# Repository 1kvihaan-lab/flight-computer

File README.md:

# Stardance — ESP32-S3 Multi-Sensor Telemetry Board

A compact, single-board data logger built around an **ESP32-S3** class module with
**GNSS positioning**, **three-axis motion sensing**, **barometric altitude**, a
**battery-backed real-time clock**, and a **high-side current/power monitor**.

The board is designed to be built cheaply and in small volumes: two copper layers,
1.6 mm FR4, no impedance-controlled traces, no castellations, no fine-pitch
microvias. Everything on it can be assembled by a standard turnkey PCBA service
such as PCBWay.

---

## Table of contents

1. [What the board does](#what-the-board-does)
2. [At a glance](#at-a-glance)
3. [Functional blocks](#functional-blocks)
4. [Board mechanicals](#board-mechanicals)
5. [Power architecture](#power-architecture)
6. [Net and interface summary](#net-and-interface-summary)
7. [Bill of materials](#bill-of-materials)
8. [Fabrication notes](#fabrication-notes)
9. [Assembly notes](#assembly-notes)
10. [Cost estimate](#cost-estimate)
11. [Bring-up and test procedure](#bring-up-and-test-procedure)
12. [Firmware interface](#firmware-interface)
13. [Known issues](#known-issues)
14. [Design rules and constraints](#design-rules-and-constraints)
15. [Revision history](#revision-history)
16. [File inventory](#file-inventory)
17. [Licence](#licence)

---

## What the board does

Stardance is a **sensor fusion and position logger**. In one small board it
combines:

- an **ESP32-S3** module with onboard antenna — the compute, Wi-Fi and BLE radio,
- a **u-blox MAX-M10S** GNSS receiver — position, velocity and precise time,
- an **ADXL372** — high-g, low-power accelerometer for shock and impact events,
- an **LSM6DSOX** — 6-axis IMU for orientation and motion context,
- a **BMP388** — barometric pressure and temperature, for altitude,
- a **PCF8563T** RTC with a 32.768 kHz crystal — timekeeping across power cycles,
- an **INA228** — 20-bit current, voltage and power monitoring,
- a **USB-C** receptacle for power and data,
- an **AP2112K-3.3** LDO for the 3.3 V rail.

The design intent is a board that can answer, simultaneously: *where am I, how
fast am I moving, how did I get knocked around, how high am I, what time is it,
and how much energy have I actually used?* That combination is useful for
wearables, sports instrumentation, drone and rocket flight recorders, field
survey equipment, and any battery-powered device where you want to log motion
plus position plus power draw over a long deployment.

Because all of the sensors sit on shared I²C and SPI buses behind a single
microcontroller, the board can be configured at runtime for either a
high-rate short-duration capture (IMU at 1.6 kHz, streaming over USB/Wi-Fi) or a
low-rate long-duration log (one GNSS fix every few minutes, everything else in
its lowest-power mode, data to flash or SD).

---

## At a glance

| Parameter | Value |
| --- | --- |
| Board outline | **54.5 mm × 86.225 mm** (47.0 cm²) |
| Copper layers | **2** (F.Cu, B.Cu) |
| Board thickness | 1.6 mm |
| Surface finish | ENIG recommended (LGA land patterns) |
| Solder mask | Both sides, 0.05 mm mask expansion |
| Silkscreen | Both sides |
| Minimum via drill | 0.20 mm |
| Minimum track width used | 0.1124 mm |
| Largest / most critical part | ADXL372, 16-pad 3.0 × 3.25 mm LGA |
| Mounting | 4 × mounting holes |
| Programming | USB-C + 2 × 5 pin header |
| Design tool | KiCad |
| Source schematic | `StardancePCB.kicad_sch` |
| PCB file | `StardancB.kicad_pcb` |

---

## Functional blocks

### Compute and radio — ESP32-S3 module with onboard antenna

An ESP32-S3-based module carrying the SoC, flash, the RF front end and a PCB
antenna. Using the module rather than a bare chip keeps the RF layout off this
board entirely, which is what makes a two-layer design viable.

The module provides the SPI and I²C buses that all sensors hang from, the USB
peripheral used for programming and data streaming, and general-purpose I/O for
interrupts and control lines.

**Layout note:** the antenna end of the module overhangs or sits at the board
edge with a copper keep-out region beneath and beside it. Do not place metal,
battery or enclosure hardware in that zone, and do not pour ground under the
antenna. When the board is installed, the antenna side should face away from the
battery.

### GNSS — u-blox MAX-M10S

A concurrent multi-constellation GNSS receiver (GPS, GLONASS, Galileo, BeiDou)
with a very low tracking current. It talks over UART or I²C depending on
configuration, and needs a clean, well-decoupled supply — hence the dedicated
`/GNSS_VCC` rail rather than sharing the noisy 3.3 V sensor rail directly.

**Design notes:**

- Keep the GNSS supply trace short and well bypassed; GNSS receivers are
  sensitive to supply noise and to nearby switching regulators.
- The receiver needs a clear view of the sky. In an enclosure, the antenna must
  not be under metal.
- If no active antenna is fitted, provide an antenna connection (u.FL/SMA) per
  the module's reference design.
- The first fix after a cold start takes tens of seconds outdoors; this is
  normal and not a fault.

### Motion — ADXL372 and LSM6DSOX

Two complementary accelerometer devices:

- **ADXL372 (U11)** — a 3-axis, high-g accelerometer intended for impact and
  shock detection. It has an internal FIFO and an event engine, and it can wake
  the host on threshold. Its interrupt line `/ADXL_INT` and chip select
  `/ADXL_CS` are routed to the module; it shares SPI with the bus on `/SPI_SCK`.
- **LSM6DSOX** — a 6-axis accelerometer plus gyroscope with an embedded
  machine-learning core, used for orientation, gait or gesture classification
  and general motion context.

The split is deliberate: the ADXL372 is the shock witness and the LSM6DSOX is
the orientation reference, so an impact event does not saturate or corrupt the
data you use for attitude.

**Package note:** the ADXL372 in this design is the
`BCCZ` 16-terminal LGA, 3.0 × 3.25 mm (JEDEC CC-16-4). It is *not*
pin-compatible with the ADXL363, which shares the package outline, so do not
substitute one for the other in assembly. Pin 5 is `MISO` on one part and
reserved on the other, pin 7 and pin 8 also differ. The land pattern used here
is `PQFN50P322X300X114-16N`.

**Mask note:** the LGA apertures on this board are drawn 1:1 with the copper
pads, i.e. **zero solder-mask expansion**. This is intentional for LGA parts —
it prevents solder bridging between adjacent pads under the body — but it means
the fab must honour a zero mask expansion on those apertures rather than
applying its own default. Two DRC warnings about mask aperture bridging on these
pads are expected and accepted.

### Pressure and altitude — BMP388

A piezo-resistive absolute pressure sensor with temperature output. Used for
barometric altitude and for vertical-velocity estimation. It is sensitive to
light and to airflow, so the datasheet calls for a small vent or a light-blocking
underfill around the port. Relative altitude from barometric pressure drifts with
weather, so treat it as short-term relative altitude, not absolute height.

### Timekeeping — PCF8563T + 32.768 kHz crystal

An I²C real-time clock with a battery-backed supply so that time survives main
power removal. The crystal is an `FC-135`-style 32.768 kHz tuning-fork part in a
3.2 × 1.5 mm SMD package.

**Layout note:** the crystal is placed close to the RTC with short traces and a
local ground guard. Do not route high-speed signals under or beside it; a
tuning-fork crystal is a high-impedance resonator and will pick up coupling.

Time discipline: the ESP32-S3's own RTC is adequate for seconds-level accuracy
but drifts with temperature. The PCF8563 plus GNSS time on fix gives you a
board that always knows the correct time within a second or so of the last fix.

### Power monitoring — INA228

A 20-bit I²C current, bus-voltage and power monitor with an integrated charge and
energy accumulator. On this board it measures through a **10 mΩ shunt** on the
battery path, so it sees the real load current of the whole board rather than a
regulated rail current. The energy accumulator makes it possible to report
"joules consumed since boot" directly, which is a much more honest power figure
than multiplying an instantaneous reading by elapsed time.

Because the shunt is only 10 mΩ, the full-scale current range is set by the
INA228's programmable gain and the shunt value — check the configured range
against your expected peak current before trusting readings, since a large
inrush (the ESP32 waking and transmitting) can exceed a conservative setting.

### Power supply — AP2112K-3.3

A 600 mA low-dropout regulator providing the 3.3 V rail. It is a linear
regulator: simple, quiet, and low part count, at the cost of dissipating
`(Vin − 3.3) × Iload` as heat. With a Li-ion cell at 4.2 V and 200 mA of load
that is about 0.18 W, which is fine in free air but worth checking in a sealed
enclosure.

The regulator is deliberately used instead of a buck converter for the sensor
rail because GNSS and precision analogue measurements care more about supply
noise than about a few tens of milliwatts.

### USB-C and connectors

- **USB-C receptacle** — `HRO TYPE-C-31-M-12`, 14-pin USB 2.0-only variant. It
  provides 5 V in, USB 2.0 data to the module, and the usual CC pull-down
  resistors (5.1 kΩ) so that a USB-C host supplies 5 V. It is *not* a USB-PD
  port.
- **2 × 5 pin header** (`Conn_02x05_Odd_Even`) — debug / programming / expansion.
- **1 × 4 pin header** (`Conn_01x04_Pin`) — secondary connector, typically used
  for a serial console or an external sensor.
- **Test points** — several, for probing the main rails and buses during bring-up.
- **4 × mounting holes.**

---

## Board mechanicals

The board outline is a single rectangle on `Edge.Cuts`:

```
gr_rect (start 97.5 95.5) (end 152 181.725)
```

giving **54.5 mm × 86.225 mm**, or 46.99 cm².

- **Enclosure allowance:** if you are quoting or modelling an enclosure, allow
  about 55 × 87 mm internal, plus 0.5 mm clearance per side for the mask and
  routing tolerance, plus room for the USB-C overhang if the connector is
  flush-mounted.
- **Standoffs:** four mounting holes; use M2 or M2.5 hardware and keep the
  corresponding keep-out area free of components on the underside.
- **Antenna zone:** keep metal and battery out of the module antenna keep-out.
- **Connector access:** USB-C is at approximately (125, 175.5) in board
  coordinates — check that your enclosure gives it a suitable cutout and that
  the cable can plug in without strain.

---

## Power architecture

```
USB-C 5 V ──► /USB_5V ──┬──► AP2112K-3.3 ──► +3V3 ──► ESP32-S3, sensors, RTC
                        │
                        └──► charge path ──► /BAT_PROT ──► /BAT_LOAD ──► 10 mΩ shunt ──► INA228
```

- **`/USB_5V`** — raw 5 V from USB, present only when a cable is connected.
- **`/BAT_PROT`** — battery node downstream of protection (over-discharge and
  over-current), so the cell cannot be damaged by a firmware bug.
- **`/BAT_LOAD`** — the switched/monitored load side.
- **`+3V3`** — the regulated rail feeding the module and all sensors.
- **`/GNSS_VCC`** — a separately decoupled branch for the GNSS receiver so that
  the module's transmit bursts do not disturb the receiver's supply.
- A **Schottky diode** provides reverse-polarity and back-feed protection between
  the supply sources, and a **600 Ω @ 100 MHz ferrite bead** filters high-frequency
  noise out of a supply branch.

Practically: the board runs from USB alone, from a battery alone, or from both
with the battery charging. When you measure power with the INA228, remember that
USB presence changes the current path — log the USB state alongside the current
reading or the numbers will not make sense.

---

## Net and interface summary

| Net | Purpose |
| --- | --- |
| `+3V3` | Regulated 3.3 V rail |
| `/USB_5V` | 5 V from USB-C |
| `/BAT_PROT` | Protected battery node |
| `/BAT_LOAD` | Monitored battery load node |
| `/GNSS_VCC` | Filtered supply for the GNSS receiver |
| `I2C_SDA` / `I2C_SCL` | Shared I²C bus (BMP388, LSM6DSOX, PCF8563T, INA228) |
| `SPI_SCK` | Shared SPI clock (ADXL372) |
| `/ADXL_CS` | ADXL372 chip select |
| `/ADXL_INT` | ADXL372 interrupt / event line |
| `/PWM2` | General-purpose PWM output |

The I²C bus carries several devices with different addresses; confirm the address
straps (the `SA0`/`SDO` style pins) do not collide before writing firmware.

---

## Bill of materials

The table below lists the significant parts. Quantities for passives are
approximate because the exact count comes from the KiCad position file; the
authoritative BOM is the one exported from the schematic.

| Ref | Part | Function | Qty | Est. unit price (10-off) |
| --- | --- | --- | --- | --- |
| U? | ESP32-S3 module, onboard antenna, SMD | MCU + Wi-Fi/BLE | 1 | $4 – $6 |
| U? | MAX-M10S | GNSS receiver | 1 | $14 – $20 |
| U11 | ADXL372BCCZ-RL7 | High-g accelerometer | 1 | $14 – $20 |
| U? | LSM6DSOX | 6-axis IMU | 1 | $4 – $7 |
| U? | BMP388 | Pressure / altitude | 1 | $2.50 – $4 |
| U? | PCF8563T | RTC | 1 | $1 – $2 |
| Y1 | FC-135 32.768 kHz, 3.2 × 1.5 mm | RTC crystal | 1 | $0.50 – $1 |
| U? | INA228 | Current / power monitor | 1 | $5 – $8 |
| U? | AP2112K-3.3 | 3.3 V LDO | 1 | $0.25 – $0.50 |
| J? | USB-C receptacle, HRO TYPE-C-31-M-12 | Power + data | 1 | $0.80 – $1.50 |
| J? | `Conn_02x05_Odd_Even` | Debug / expansion | 1 | $0.30 – $0.80 |
| J? | `Conn_01x04_Pin` | Auxiliary | 1 | $0.20 – $0.50 |
| R? | 10 mΩ shunt | Current sense | 1 | $0.30 – $1.00 |
| D? | Schottky diode | Reverse / back-feed protection | 1 | $0.20 – $0.60 |
| FB? | 600 Ω @ 100 MHz ferrite | Supply filtering | 1 | $0.05 – $0.20 |
| — | Passives: 10 k, 100 k, 100 R, 52.3 k, 5.1 k, 4.7 k, 1 µF, 100 nF, 10 nF, 15 pF, 4.7 nF, 10 µF, 22 µF | Decoupling, pull-ups, filters, timing | ~55 – 70 | $1.50 – $3.00 total |
| — | Test points, mounting holes | Bring-up / mechanical | ~9 | negligible |

**Estimated parts cost: $50 – $75 per board** at 10-off distributor pricing.
Most of that cost sits in three parts: the GNSS receiver, the ADXL372, and the
ESP32-S3 module. Everything else is small change.

Notes:

- `52.3 k` and `15 pF` are typical GNSS/oscillator or divider values — check them
  against the reference design of the specific module variant you buy.
- `5.1 k` on the USB-C CC pins is mandatory; without it a USB-C host will not
  supply 5 V.
- The 10 mΩ shunt should be a low-TCR, low-inductance part; a generic thick-film
  resistor will give you temperature- and frequency-dependent current readings.

---

## Fabrication notes

Send these with the order, or attach them as a README in the fab package:

1. **Layers:** 2, 1.6 mm thick, 1 oz copper both sides.
2. **Finish:** ENIG. The two LGA land patterns and the fine-pitch parts benefit
   from a flat finish; HASL is acceptable but makes LGA placement less reliable.
3. **Mask:** standard, **but honour the 1:1 (zero-expansion) apertures on the
   ADXL372 and LGA pads**. Do not apply a global mask expansion on those.
4. **Min drill:** 0.20 mm — this meets the standard 0.20 mm minimum CNC drill at
   the usual low-cost services. Do not request 0.15 mm drills.
5. **Impedance control:** not required.
6. **Castellations:** none.
7. **Panelisation:** the board is 54.5 mm on the short edge. Ask the fab whether
   it will be panelised; if so, confirm the mouse-bite or V-score positions and
   that no components sit within the breakaway zone.
8. **Silkscreen:** keep clear of pads; the reference designators are needed for
   hand rework.
9. **Edge clearance:** confirm no copper closer than 0.3 mm to the outline.

Deliver: Gerbers (RS-274X), Excellon drill file, and a fab drawing. Include the
board thickness and finish in the fab drawing rather than relying on file names.

---

## Assembly notes

The assembly is a straightforward single-sided SMT job plus a USB-C connector.

- **Sides:** all SMT parts on the top side. No bottom-side SMT, so no double
  reflow and no second stencil.
- **Joints:** roughly 220 – 260 SMT joints, dominated by passives.
- **Unique parts:** roughly 70 – 85 line items including passives.
- **Process:** lead-free reflow, IPC-A-610 Class 2 is sufficient for a prototype.
- **THT:** the headers and any through-hole parts can be hand-soldered or
  wave-soldered; specify which.
- **Turnkey vs consigned:** turnkey (the assembler sources the parts) is simpler
  and avoids shipping reels around, but you pay a markup and you inherit their
  stock risk. Consigned (you buy from a distributor and ship the parts) is
  cheaper on parts but shifts the logistics and any shortage onto you.

**Parts to check for stock before you commit:** the MAX-M10S and the ADXL372 are
the two expensive, long-lead items on this board. Ask for a stock date before
confirming a build date, and if either is out of stock, decide up front whether
you will accept a substitute — for the ADXL372, there is no drop-in equivalent
in the same footprint.

---

## Cost estimate

Prices below are ballpark figures for a small prototype run through a turnkey
PCBA service (PCBWay or equivalent). They are for budgeting only; the real
number comes from the vendor's generated quote.

### Two boards

| Line | Basis | Estimate |
| --- | --- | --- |
| PCB fabrication | Minimum order is typically 5 pcs; 10 pcs of this size is ~$5 | $5 – $10 |
| Assembly setup + stencil + labour | One-time setup dominates at this quantity | $80 – $120 |
| Components | 2 – 5 sets, see BOM | $100 – $150 |
| Shipping (DHL/FedEx) | ~1 kg | $40 – $60 |
| **Total** | | **$230 – $350** |
| Realistic outcome | Assemblers have a 5-piece minimum | **~$300 for 5 boards** |

### Ten boards

| Line | Estimate |
| --- | --- |
| PCB fabrication | $5 – $30 |
| Assembly (setup + labour) | $150 – $250 |
| Components (10 sets) | $500 – $750 |
| Shipping | $40 – $80 |
| **Total** | **$700 – $1,100** |
| **Unit cost** | **$70 – $110 per board** |

The important lesson from both tables: **at prototype quantities the PCB is
almost free and the money is in parts and assembly setup.** Unit cost falls
mainly by spreading the setup fee — at 50 pcs the setup cost per board drops by
roughly 5×, and component pricing improves another 15 – 30 %.

To get a vendor quote, fill in the PCBA form with approximately **250 SMT
joints** and **75 unique parts**, 2 layers, 54.5 × 86.23 mm, and turnkey
sourcing. Save the resulting PDF quote with its date so the number is traceable.

---

## Bring-up and test procedure

Do these in order. Do not skip steps — a fault found at step 9 costs you a whole
board, and a fault found at step 3 costs you a resistor.

### 1. Visual inspection, unpowered

- Check for solder bridges on the two LGA parts, the USB-C pins, and the fine
  passives. Use a microscope; the LGA pitch is too fine for naked-eye inspection.
- Confirm no components are missing or rotated, and that polarity marks match.
- Confirm no copper slivers or unplated edges.

### 2. Continuity, unpowered

- `+3V3` to `GND`: should read high resistance (tens of kΩ or more), not a short.
- `/USB_5V` to `GND`: same.
- `/BAT_PROT` to `/BAT_LOAD`: should read approximately the shunt value plus the
  protection path resistance.
- Every I²C and SPI line to `GND`: no shorts.

If `+3V3` reads a short, find it before applying power.

### 3. First power, current-limited

- Apply 5 V from a bench supply **with the current limit set to about 100 mA**.
- Watch the draw. A healthy idle board draws a few tens of mA; a board that
  slams into the limit has a short.
- Measure `+3V3` — should be 3.28 – 3.32 V.
- Measure `/GNSS_VCC` — should be present and close to 3.3 V.

### 4. USB enumeration

- Connect to a PC over USB-C. The ESP32-S3 should enumerate (native USB or a
  USB-serial bridge, depending on the module variant).
- Confirm 5 V is present on `/USB_5V` and the CC pull-downs are working — a
  USB-C-to-C cable from a USB-C host is the strict test; an A-to-C cable will
  work even with the CC resistors missing.

### 5. Module boot and programming

- Program a blink or serial-print sketch over USB.
- Confirm the module boots and the serial console works at the expected baud.
- Confirm the 2 × 5 header gives you access to the boot/reset lines if you use
  them.

### 6. I²C bus scan

- Scan the I²C bus and confirm every device answers at its expected address:
  BMP388, LSM6DSOX, PCF8563T, INA228.
- A missing device means a solder joint, a wrong address strap, or a
  non-populated part. A device answering at an unexpected address means an
  address pin is strapped differently than assumed.

### 7. Sensor sanity

- Read die temperature from each device — they should agree within a few degrees
  and match room temperature.
- Read the BMP388 pressure — near 1013 hPa at sea level, and it should change
  when you gently press or release near the port.
- Read the LSM6DSOX accelerometer — with the board flat, one axis reads about
  1 g; tilt the board and watch the vector rotate.
- Read the ADXL372 — confirm it responds on SPI and that `/ADXL_INT` toggles
  when you tap the board.
- Read the RTC — set a time, remove power for a minute, restore power, and
  confirm the time kept running.

### 8. Power monitor calibration

- With a known resistive load, compare the INA228 current reading against a
  multimeter in series.
- Confirm the sign convention, the shunt value in the configuration register,
  and the full-scale range. A wrong shunt value in firmware gives readings that
  are off by a constant factor — check it now, not later.

### 9. GNSS

- Go outdoors with a clear sky view. Cold start to first fix typically takes
  20 – 60 seconds. If you get no fix in five minutes outdoors, check the supply,
  the antenna connection and the UART/I²C configuration.
- Confirm the reported time matches reality to within a second.
- Compare the reported position to a known point.

### 10. Radio

- Confirm Wi-Fi association and BLE advertising.
- Check RSSI at a few metres. A weak or absent signal usually means metal or a
  battery over the antenna keep-out.

### 11. Thermal

- Run the board for ten minutes at your expected load and check the LDO and the
  module temperature by touch or IR. The LDO is the part that will get warm.

Record every measurement. A bring-up log with nominal values makes the second
board far easier to debug.

---

## Firmware interface

Firmware is not included in this repository; this section documents what the
hardware expects.

| Peripheral | Bus | Pins / nets | Notes |
| --- | --- | --- | --- |
| ESP32-S3 module | — | — | Native USB or bridge UART for programming |
| MAX-M10S | UART or I²C | `/GNSS_VCC` supply | Configure protocol at init |
| ADXL372 | SPI | `SPI_SCK`, `/ADXL_CS`, `/ADXL_INT` | Interrupt is the cheap way to detect impacts |
| LSM6DSOX | I²C | `I2C_SDA`, `I2C_SCL` | Optional interrupt pin if wired |
| BMP388 | I²C | `I2C_SDA`, `I2C_SCL` | Needs a conversion-time delay between reads |
| PCF8563T | I²C | `I2C_SDA`, `I2C_SCL` | Battery-backed; set once, read thereafter |
| INA228 | I²C | `I2C_SDA`, `I2C_SCL` | Configure shunt value and range before reading |
| PWM output | GPIO | `/PWM2` | General purpose |

Practical firmware advice:

- **Initialise I²C once, share the bus.** All four I²C devices live on the same
  two wires. Take a mutex or serialise access, or a long sensor read will
  collide with an RTC read and one of them will return garbage.
- **Use the ADXL372 FIFO**, not a polling loop. Polling a high-g part at high
  rate wakes the CPU constantly and burns the battery you are trying to measure.
- **Use GNSS time to discipline the RTC.** The RTC is accurate to tens of ppm;
  GNSS gives you absolute time. Re-sync on every fix.
- **Log the USB state with the current reading.** Otherwise your power data has
  an unexplained step in it wherever a cable was plugged in.
- **Deep sleep order matters.** Put the sensors to sleep first, then the GNSS,
  then the module. A sensor left in continuous-conversion mode will hold the
  rail up and defeat the point of sleeping.

---

## Known issues

These are open items on Rev B. Fix them before ordering a production batch.

1. **DRC is not clean.** The last full design-rule check reported unconnected
   pads in the double digits and several copper clearance violations. Unconnected
   pads mean the netlist and the layout disagree; on a two-layer board these are
   usually a forgotten via or a trace that stops one grid unit short. Run
   *Inspect → Clearance* and *Routing → Track Cleanup* and re-run DRC until it
   is empty.
2. **Solder-mask aperture bridge warnings on the LGA pads.** Expected and
   accepted: the apertures are intentionally 1:1 with the copper to prevent
   bridging under the body. Note this explicitly in the fab notes so the fab
   does not "fix" it.
3. **ERC power-output conflicts.** Multiple power-output pins on the same net
   (the regulator output pins and the GND pins on one device) plus a `PWR_FLAG`
   produce "power output and power output" errors. These are benign in KiCad
   when the pins genuinely are paralleled outputs; confirm each one rather than
   suppressing the class globally.
4. **ADXL372 land pattern provenance.** The footprint came from a
   vendor-supplied library (`PQFN50P322X300X114-16N`). Verify the pad
   dimensions and the pin-1 orientation against the ADXL372 datasheet land
   pattern before assembly — a mirrored LGA is not always visually obvious.
5. **No reverse-polarity protection on the battery connector** beyond the
   Schottky in the supply path. Confirm the connector keying physically prevents
   reverse insertion, or add a P-FET.
6. **Thermal margin of the LDO is unverified** in a sealed enclosure at full
   load. Measure before committing to a battery-only, enclosed deployment.
7. **USB-C is USB 2.0 only.** No USB-PD negotiation and no SuperSpeed. Do not
   design a charging scheme that assumes higher voltage.

---

## Design rules and constraints

The board was designed to clear the cheapest fabrication tier at common
low-cost fabs.

| Rule | Value used | Constraint |
| --- | --- | --- |
| Layers | 2 | 2-layer tier |
| Board size | 54.5 × 86.225 mm | under the 100 × 100 mm price tier |
| Min track | 0.1124 mm | above 0.10 mm |
| Min via drill | 0.20 mm | at the 0.20 mm standard minimum |
| Min via annular ring | standard | — |
| Mask expansion | 0.05 mm global, 0 mm on LGA | — |
| Board thickness | 1.6 mm | standard |
| Copper weight | 1 oz | standard |

Two-layer design consequences worth remembering: there is no solid ground plane
under the whole board, so return currents must follow their traces. Keep the
GNSS supply and the crystal traces short, keep the SPI clock away from the
crystal and the GNSS supply, and do not route signals across a plane split.

---

## Revision history

| Rev | Date | Change | Status |
| --- | --- | --- | --- |
| A | — | Initial layout | Superseded |
| B | 2026-10-29 | Two-layer rework, sensor set consolidated, LGA mask apertures set to 1:1 | DRC open, not yet built |

---

## File inventory

| File | Description |
| --- | --- |
| `StardancePCB.kicad_sch` | KiCad schematic (source of truth for the netlist) |
| `StardancB.kicad_pcb` | KiCad PCB layout, Rev B |
| `README.md` | This document |

When you generate the fabrication package, include the Gerbers, the Excellon
drill file, the BOM export, and the position (pick-and-place) file.

---

## Licence

Add your preferred licence here. For open hardware, CERN-OHL-P or CERN-OHL-S is
the usual choice; for a permissive hardware-plus-documentation release,
Apache-2.0 for the design files plus CC-BY-4.0 for the documentation also works.

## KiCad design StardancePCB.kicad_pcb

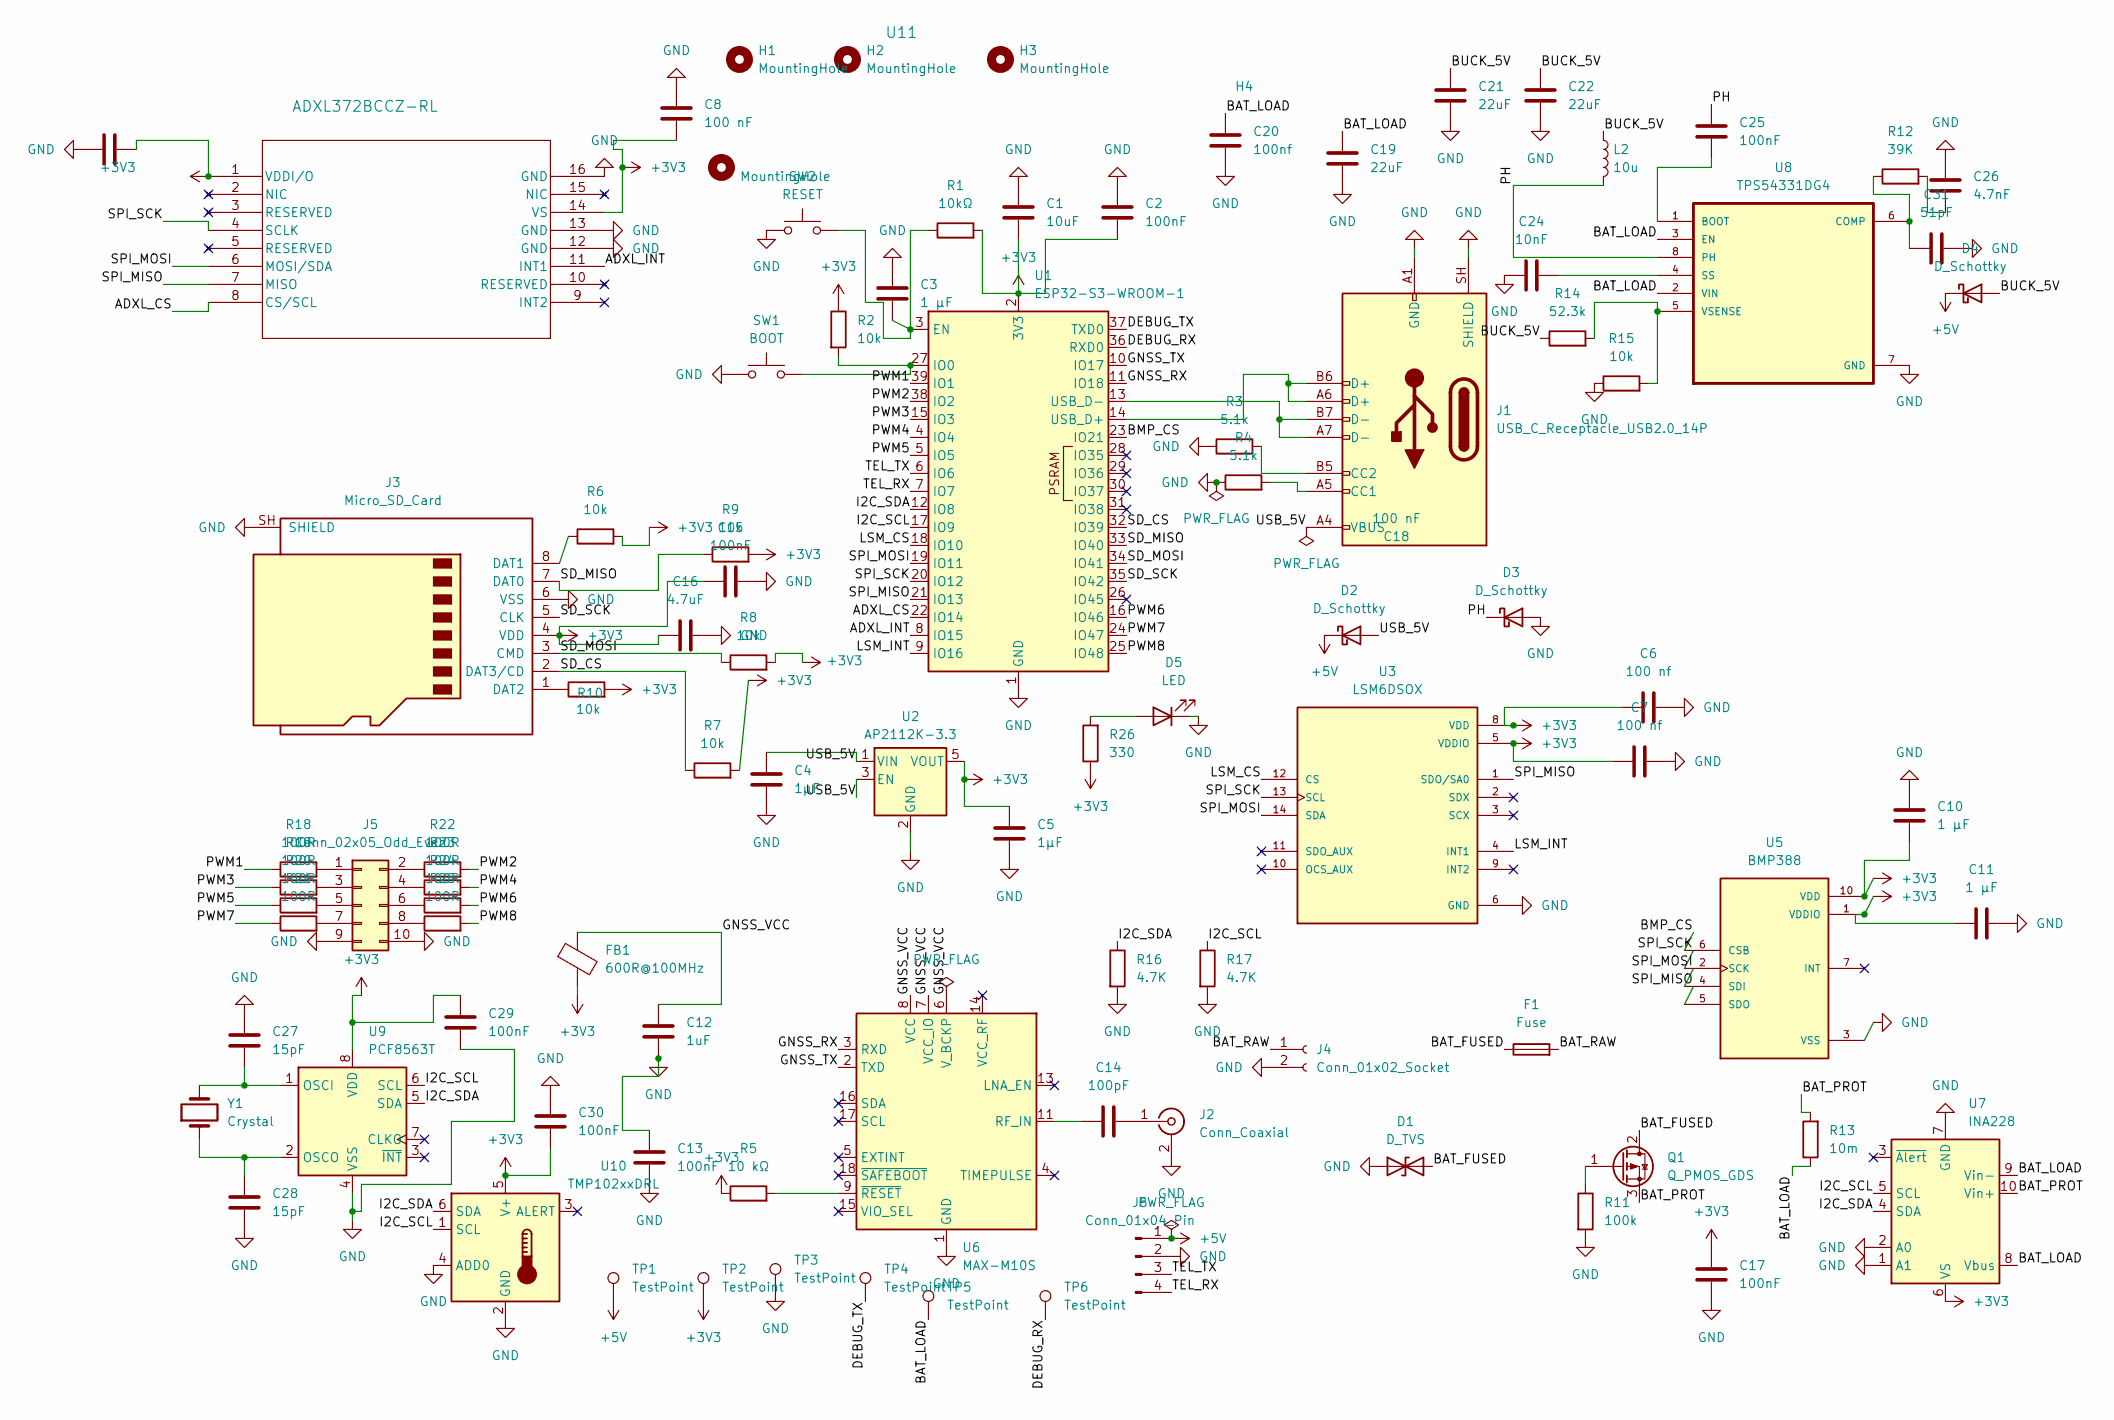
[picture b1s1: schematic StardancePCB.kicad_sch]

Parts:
C1: 10uF; C_0805_2012Metric
C2, C13, C15, C17, C25, C29, C30: 100nF; C_0603_1608Metric
C3, C10, C11: 1 µF; C_0603_1608Metric
C4, C5: 1µF; C_0603_1608Metric
C6, C7: 100 nf; C_0603_1608Metric
C8, C18: 100 nF; C_0603_1608Metric
C12: 1uF; C_0603_1608Metric
C14: 100pF; C_0603_1608Metric
C16: 4.7uF; C_0603_1608Metric
C19, C21, C22: 22uF; C_1206_3216Metric
C20: 100nf; C_0603_1608Metric
C24: 10nF; C_0603_1608Metric
C26: 4.7nF; C_0603_1608Metric
C27, C28: 15pF; C_0603_1608Metric
C31: 51pF; C_0603_1608Metric
D1: D_TVS; D_SMA
D2, D3, D4: D_Schottky; D_SMA
D5: LED; LED_0805_2012Metric
F1: Fuse; Fuse_1206_3216Metric
FB1: 600R@100MHz; L_0805_2012Metric
H1, H2, H3, H4: MountingHole; MountingHole_3.2mm_M3
J1: USB_C_Receptacle_USB2.0_14P; USB_C_Receptacle_HRO_TYPE-C-31-M-12
J2: Conn_Coaxial; U.FL_Hirose_U.FL-R-SMT-1_Vertical
J3: Micro_SD_Card; microSD_HC_Hirose_DM3AT-SF-PEJM5
J4: Conn_01x02_Socket; PinSocket_1x02_P2.54mm_Vertical
J5: Conn_02x05_Odd_Even; PinHeader_2x05_P2.54mm_Vertical
J6: Conn_01x04_Pin; PinHeader_1x04_P2.54mm_Vertical
L2: 10u; L_7.3x7.3_H3.5
Q1: Q_PMOS_GDS; SOT-23
R1: 10kΩ; R_0603_1608Metric
R2, R6, R7, R8, R9, R10, R15: 10k; R_0603_1608Metric
R3, R4: 5.1k; R_0603_1608Metric
R5: 10 kΩ; R_0603_1608Metric
R11: 100k; R_0603_1608Metric
R12: 39K; R_0603_1608Metric
R13: 10m; R_2512_6332Metric
R14: 52.3k; R_0603_1608Metric
R16, R17: 4.7K; R_0603_1608Metric
R18, R19, R20, R21, R22, R23, R24, R25: 100R; R_0603_1608Metric
R26: 330; R_0603_1608Metric
SW1: BOOT; SW_PUSH_6mm
SW2: RESET; SW_PUSH_6mm
TP1, TP2, TP3, TP4, TP5, TP6: TestPoint; TestPoint_Pad_1.5x1.5mm
U1: ESP32-S3-WROOM-1
U2: AP2112K-3.3; SOT-23-5
U3: LSM6DSOX; LGA-14_3x2.5mm_P0.5mm_LayoutBorder3x4y; PARTREV 3.0
U5: BMP388; XDCR_BMP388; PARTREV 1.7
U6: MAX-M10S; ublox_MAX
U7: INA228; TSSOP-10_3x3mm_P0.5mm
U8: TPS54331DG4; SOIC127P599X175-8N
U9: PCF8563T; SOIC-8_3.9x4.9mm_P1.27mm
U10: TMP102xxDRL; SOT-563
U11: ADXL372BCCZ-RL; PQFN50P322X300X114-16N
Y1: Crystal; Crystal_SMD_3215-2Pin_3.2x1.5mm

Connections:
+3V3: C1.2, C2.2, C5.1, C6.1, C7.1, C8.2, C10.2, C11.1, C15.1, C16.1, C17.1, C18.2, C29.1, C30.2, FB1.2, J3.4 (VDD), R1.2, R2.1, R5.1, R6.2, R7.2, R8.2, R9.2, R10.2, R26.1, TP2.1 (1_1), U1.2 (3V3), U2.5 (VOUT), U3.5 (VDDIO), U3.8 (VDD), U5.1 (VDDIO), U5.10 (VDD), U7.6 (VS), U9.8 (VDD), U10.5 (V+), U11.1 (VDDI/O), U11.14 (VS); also elsewhere on the board
+5V: D2.1 (K), D4.1 (K), J6.1, TP1.1 (1_1)
/ADXL_CS: U1.22 (IO14), U11.8 (CS/SCL)
/ADXL_INT: U1.8 (IO15), U11.11 (INT1)
/BAT_FUSED: D1.2 (A2), F1.1, Q1.2 (D)
/BAT_LOAD: C19.1, C20.1, R13.1, TP5.1 (1_1), U7.8 (Vbus), U7.9 (Vin-), U8.2 (VIN), U8.3 (EN)
/BAT_PROT: Q1.3 (S), R13.2, U7.10 (Vin+)
/BAT_RAW: F1.2, J4.1
/BMP_CS: U1.23 (IO21), U5.6 (CSB)
/BUCK_5V: C21.1, C22.1, D4.2 (A), L2.1, R14.1
/DEBUG_RX: TP6.1 (1_1), U1.36 (RXD0)
/DEBUG_TX: TP4.1 (1_1), U1.37 (TXD0)
/GNSS_RX: U1.11 (IO18), U6.3 (RXD)
/GNSS_TX: U1.10 (IO17), U6.2 (TXD)
/GNSS_VCC: C12.1, FB1.1, U6.6 (V_BCKP), U6.7 (VCC_IO), U6.8 (VCC)
/I2C_SCL: R17.1, U1.17 (IO9), U7.5 (SCL), U9.6 (SCL), U10.1 (SCL)
/I2C_SDA: R16.1, U1.12 (IO8), U7.4 (SDA), U9.5 (SDA), U10.6 (SDA)
/LSM_CS: U1.18 (IO10), U3.12 (CS)
/LSM_INT: U1.9 (IO16), U3.4 (INT1)
/PH: C25.1, D3.1 (K), L2.2, U8.8 (PH)
/PWM1: R18.1, U1.39 (IO1)
/PWM2: R22.2, U1.38 (IO2)
/PWM3: R19.1, U1.15 (IO3)
/PWM4: R23.2, U1.4 (IO4)
/PWM5: R20.1, U1.5 (IO5)
/PWM6: R24.2, U1.16 (IO46)
/PWM7: R21.1, U1.24 (IO47)
/PWM8: R25.2, U1.25 (IO48)
/SD_CS: J3.2 (DAT3/CD), R7.1, U1.32 (IO39)
/SD_MISO: J3.7 (DAT0), R9.1, U1.33 (IO40)
/SD_MOSI: J3.3 (CMD), R8.1, U1.34 (IO41)
/SD_SCK: J3.5 (CLK), U1.35 (IO42)
/SPI_MISO: U1.21 (IO13), U3.1 (SDO/SA0), U5.5 (SDO), U11.7 (MISO)
/SPI_MOSI: U1.19 (IO11), U3.14 (SDA), U5.4 (SDI), U11.6 (MOSI/SDA)
/SPI_SCK: U1.20 (IO12), U3.13 (SCL), U5.2 (SCK), U11.4 (SCLK)
/TEL_RX: J6.4, U1.7 (IO7)
/TEL_TX: J6.3, U1.6 (IO6)
/USB_5V: C4.1, D2.2 (A), J1.A4 (VBUS), J1.A9 (VBUS), J1.B4 (VBUS), J1.B9 (VBUS), U2.1 (VIN), U2.3 (EN)
GND: C1.1, C2.1, C3.1, C4.2, C5.2, C6.2, C7.2, C8.1, C10.1, C11.2, C12.2, C13.1, C13.2, C15.2, C16.2, C17.2, C18.1, C19.2, C20.2, C21.2, C22.2, C24.1, C26.1, C27.1, C28.2, C29.2, C30.1, C31.2, D1.1 (A1), D3.2 (A), D5.1 (K), J1.A1 (GND), J1.A12 (GND), J1.B1 (GND), J1.B12 (GND), J1.SH (SHIELD), J2.2 (Ext), J3.6 (VSS), J3.SH (SHIELD), J4.2, J5.9, J5.10, J6.2, R3.1, R4.1, R11.2, R15.1, R16.2, R17.2, SW1.1, SW2.1, TP3.1 (1_1), U1.1 (GND), U1.40 (GND), U1.41 (GND), U2.2 (GND), U3.6 (GND), U3.7 (GND), U5.3 (VSS), U5.8 (VSS), U5.9 (VSS), U6.1 (GND), U6.10 (GND), U6.12 (GND), U7.1 (A1), U7.2 (A0), U7.7 (GND), U8.7 (GND), U9.4 (VSS), U10.2 (GND), U10.4 (ADD0), U11.12 (GND), U11.13 (GND), U11.16 (GND); also elsewhere on the board
unnamed: C26.2, R12.2
unnamed: D5.2 (A), R26.2
unnamed: J1.A5 (CC1), R4.2
unnamed: J1.B5 (CC2), R3.2
unnamed: C14.2, J2.1 (In)
unnamed: J3.8 (DAT1), R6.1
unnamed: J3.1 (DAT2), R10.1
unnamed: J5.1, R18.2
unnamed: J5.2, R22.1
unnamed: J5.3, R19.2
unnamed: J5.4, R23.1
unnamed: J5.5, R20.2
unnamed: J5.6, R24.1
unnamed: J5.7, R21.2
unnamed: J5.8, R25.1
unnamed: Q1.1 (G), R11.1
unnamed: C3.2, R1.1, SW2.2, U1.3 (EN)
unnamed: R2.2, SW1.2, U1.27 (IO0)
unnamed: J1.A6 (D+), J1.B6 (D+), U1.14 (USB_D+)
unnamed: J1.A7 (D-), J1.B7 (D-), U1.13 (USB_D-)
unnamed: C14.1, U6.11 (RF_IN)
unnamed: R5.2, U6.9 (~RESET)
unnamed: C25.2, U8.1 (BOOT)
unnamed: C31.1, R12.1, U8.6 (COMP)
unnamed: C24.2, U8.4 (SS)
unnamed: R14.2, R15.2, U8.5 (VSENSE)
unnamed: C27.2, U9.1 (OSCI), Y1.2
unnamed: C28.1, U9.2 (OSCO), Y1.1

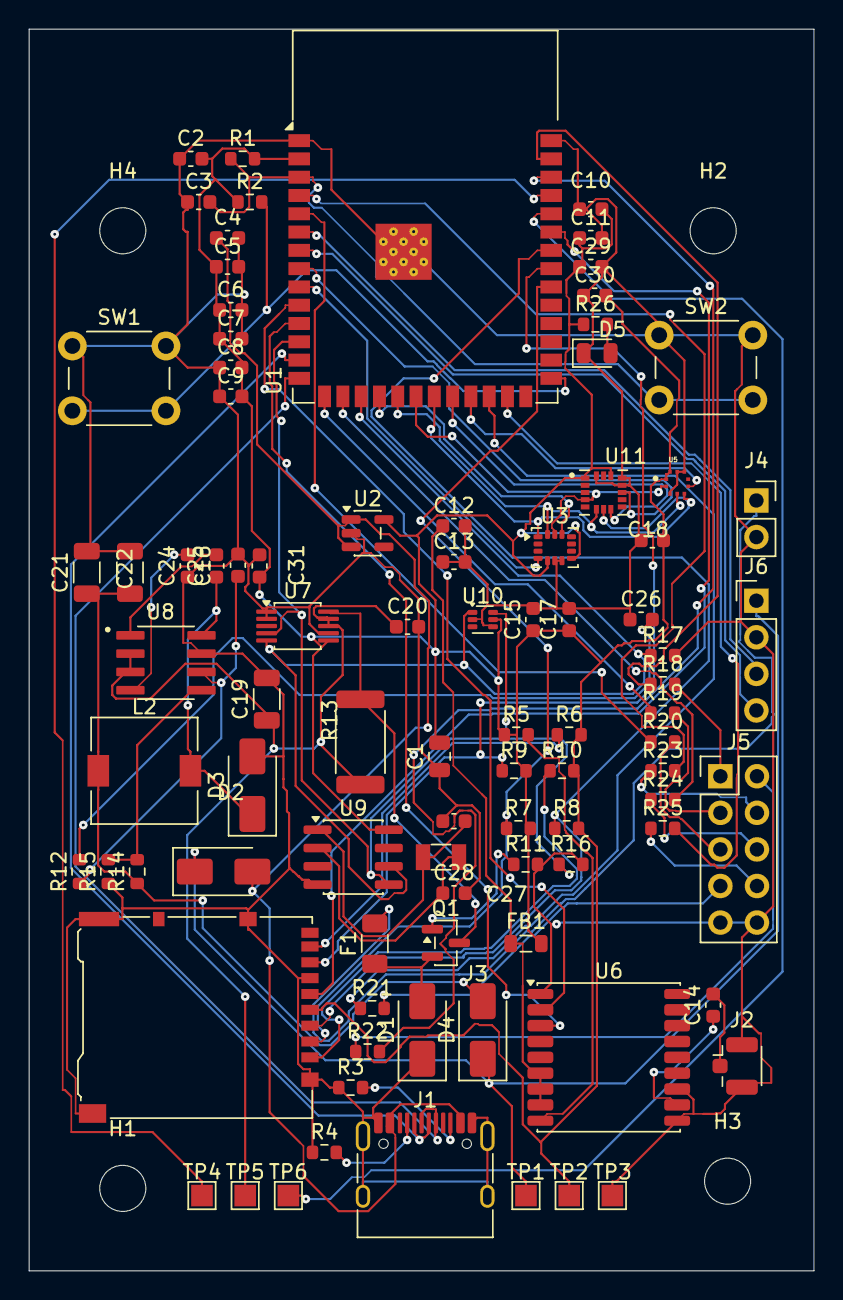
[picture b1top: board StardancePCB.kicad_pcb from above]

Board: 2 copper layers, 54.5 x 86.2 mm, 94 parts (0 on the bottom side), 67 nets.

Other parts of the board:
C9: 100 nF; C_0603_1608Metric

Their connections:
+3V3: C9.2; also elsewhere on the board
GND: C9.1; also elsewhere on the board

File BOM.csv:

"Id";"Designator";"Footprint";"Quantity";"Designation";"Supplier and ref";
1;"C1";"C_0805_2012Metric";1;"10uF";;;
2;"C2, C13, C15, C17, C25, C29, C30";"C_0603_1608Metric";7;"100nF";;;
3;"C3, C10, C11";"C_0603_1608Metric";3;"1 µF";;;
4;"C4, C5";"C_0603_1608Metric";2;"1µF";;;
5;"C6, C7";"C_0603_1608Metric";2;"100 nf";;;
6;"C8, C9, C18";"C_0603_1608Metric";3;"100 nF";;;
7;"C12";"C_0603_1608Metric";1;"1uF";;;
8;"C14";"C_0603_1608Metric";1;"100pF";;;
9;"C16";"C_0603_1608Metric";1;"4.7uF";;;
10;"C19, C21, C22";"C_1206_3216Metric";3;"22uF";;;
11;"C20";"C_0603_1608Metric";1;"100nf";;;
12;"C24";"C_0603_1608Metric";1;"10nF";;;
13;"C26";"C_0603_1608Metric";1;"4.7nF";;;
14;"C27, C28";"C_0603_1608Metric";2;"15pF";;;
15;"C31";"C_0603_1608Metric";1;"51pF";;;
16;"D1";"D_SMA";1;"D_TVS";;;
17;"D2, D3, D4";"D_SMA";3;"D_Schottky";;;
18;"D5";"LED_0805_2012Metric";1;"LED";;;
19;"F1";"Fuse_1206_3216Metric";1;"Fuse";;;
20;"FB1";"L_0805_2012Metric";1;"600R@100MHz";;;
21;"J1";"USB_C_Receptacle_HRO_TYPE-C-31-M-12";1;"USB_C_Receptacle_USB2.0_14P";;;
22;"J2";"U.FL_Hirose_U.FL-R-SMT-1_Vertical";1;"Conn_Coaxial";;;
23;"J3";"microSD_HC_Hirose_DM3AT-SF-PEJM5";1;"Micro_SD_Card";;;
24;"J4";"PinSocket_1x02_P2.54mm_Vertical";1;"Conn_01x02_Socket";;;
25;"J5";"PinHeader_2x05_P2.54mm_Vertical";1;"Conn_02x05_Odd_Even";;;
26;"J6";"PinHeader_1x04_P2.54mm_Vertical";1;"Conn_01x04_Pin";;;
27;"L2";"L_7.3x7.3_H3.5";1;"10u";;;
28;"Q1";"SOT-23";1;"Q_PMOS_GDS";;;
29;"R1";"R_0603_1608Metric";1;"10kΩ";;;
30;"R2, R6, R7, R8, R9, R10, R15";"R_0603_1608Metric";7;"10k";;;
31;"R3, R4";"R_0603_1608Metric";2;"5.1k";;;
32;"R5";"R_0603_1608Metric";1;"10 kΩ";;;
33;"R11";"R_0603_1608Metric";1;"100k";;;
34;"R12";"R_0603_1608Metric";1;"39K";;;
35;"R13";"R_2512_6332Metric";1;"10m";;;
36;"R14";"R_0603_1608Metric";1;"52.3k";;;
37;"R16, R17";"R_0603_1608Metric";2;"4.7K";;;
38;"R18, R19, R20, R21, R22, R23, R24, R25";"R_0603_1608Metric";8;"100R";;;
39;"R26";"R_0603_1608Metric";1;"330";;;
40;"SW1";"SW_PUSH_6mm";1;"BOOT";;;
41;"SW2";"SW_PUSH_6mm";1;"RESET";;;
42;"TP1, TP2, TP3, TP4, TP5, TP6";"TestPoint_Pad_1.5x1.5mm";6;"TestPoint";;;
43;"U1";"ESP32-S3-WROOM-1";1;"ESP32-S3-WROOM-1";;;
44;"U2";"SOT-23-5";1;"AP2112K-3.3";;;
45;"U3";"LGA-14_3x2.5mm_P0.5mm_LayoutBorder3x4y";1;"LSM6DSOX";;;
46;"U5";"XDCR_BMP388";1;"BMP388";;;
47;"U6";"ublox_MAX";1;"MAX-M10S";;;
48;"U7";"TSSOP-10_3x3mm_P0.5mm";1;"INA228";;;
49;"U8";"SOIC127P599X175-8N";1;"TPS54331DG4";;;
50;"U9";"SOIC-8_3.9x4.9mm_P1.27mm";1;"PCF8563T";;;
51;"U10";"SOT-563";1;"TMP102xxDRL";;;
52;"U11";"PQFN50P322X300X114-16N";1;"ADXL372BCCZ-RL";;;
53;"Y1";"Crystal_SMD_3215-2Pin_3.2x1.5mm";1;"Crystal";;;
